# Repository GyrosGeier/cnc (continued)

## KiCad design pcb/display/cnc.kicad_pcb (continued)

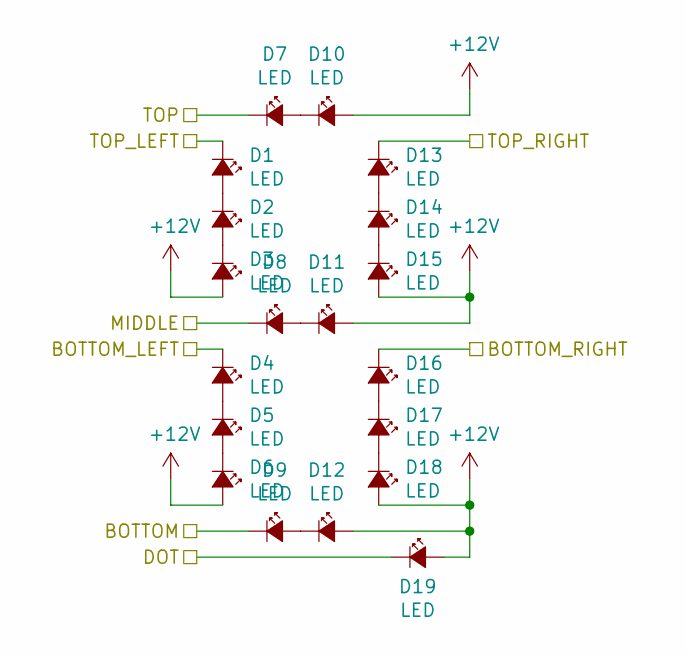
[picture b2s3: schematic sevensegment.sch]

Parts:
D1, D2, D3, D4, D5, D6, D7, D8, D9, D10, D11, D12, D13, D14, D15, D16, D17, D18, D19: LED; LED_Osram_LG_T770

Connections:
+12V: D3.2 (A), D6.2 (A), D10.2 (A), D11.2 (A), D12.2 (A), D15.2 (A), D18.2 (A), D19.2 (A); also elsewhere on the board
/display/display_x1_x2/sevensegment_1/BOTTOM: D9.1 (K); also elsewhere on the board
/display/display_x1_x2/sevensegment_1/BOTTOM_LEFT: D4.1 (K); also elsewhere on the board
/display/display_x1_x2/sevensegment_1/BOTTOM_RIGHT: D16.1 (K); also elsewhere on the board
/display/display_x1_x2/sevensegment_1/DOT: D19.1 (K); also elsewhere on the board
/display/display_x1_x2/sevensegment_1/MIDDLE: D8.1 (K); also elsewhere on the board
/display/display_x1_x2/sevensegment_1/TOP: D7.1 (K); also elsewhere on the board
/display/display_x1_x2/sevensegment_1/TOP_LEFT: D1.1 (K); also elsewhere on the board
/display/display_x1_x2/sevensegment_1/TOP_RIGHT: D13.1 (K); also elsewhere on the board
unnamed: D1.2 (A), D2.1 (K)
unnamed: D2.2 (A), D3.1 (K)
unnamed: D4.2 (A), D5.1 (K)
unnamed: D5.2 (A), D6.1 (K)
unnamed: D7.2 (A), D10.1 (K)
unnamed: D8.2 (A), D11.1 (K)
unnamed: D9.2 (A), D12.1 (K)
unnamed: D13.2 (A), D14.1 (K)
unnamed: D14.2 (A), D15.1 (K)
unnamed: D16.2 (A), D17.1 (K)
unnamed: D17.2 (A), D18.1 (K)

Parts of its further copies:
D20, D21, D22, D23, D24, D25, D26, D27, D28, D29, D30, D31, D32, D33, D34, D35, D36, D37, D38, D39, D40, D41, D42, D43, D44, D45, D46, D47, D48, D49, D50, D51, D52, D53, D54, D55, D56, D57, D58, D59, D60, D61, D62, D63, D64, D65, D66, D67, D68, D69, D70, D71, D72, D73, D74, D75, D76, D77, D78, D79, D80, D81, D82, D83, D84, D85, D86, D87, D88, D89, D90, D91, D92, D93, D94, D95, D96, D97, D98, D99, D100, D101, D102, D103, D104, D105, D106, D107, D108, D109, D110, D111, D112, D113, D114, D115, D116, D117, D118, D119, D120, D121, D122, D123, D124, D125, D126, D127, D128, D129, D130, D131, D132, D133, D134, D135, D136, D137, D138, D139, D140, D141, D142, D143, D144, D145, D146, D147, D148, D149, D150, D151, D152, D153, D154, D155, D156, D157, D158, D159, D160, D161, D162, D163, D164, D165, D166, D167, D168, D169, D170, D171, D172, D173, D174, D175, D176, D177, D178, D179, D180, D181, D182, D183, D184, D185, D186, D187, D188, D189, D190, D191, D192, D193, D194, D195, D196, D197, D198, D199, D200, D201, D202, D203, D204, D205, D206, D207, D208, D209, D210, D211, D212, D213, D214, D215, D216, D217, D218, D219, D220, D221, D222, D223, D224, D225, D226, D227, D228, D229, D230, D231, D232, D233, D234, D235, D236, D237, D238, D239, D240, D241, D242, D243, D244, D245, D246, D247, D248, D249, D250, D251, D252, D253, D254, D255, D256, D257, D258, D259, D260, D261, D262, D263, D264, D265, D266, D267, D268, D269, D270, D271, D272, D273, D274, D275, D276, D277, D278, D279, D280, D281, D282, D283, D284, D285, D286, D287, D288, D289, D290, D291, D292, D293, D294, D295, D296, D297, D298, D299, D300, D301, D302, D303, D304, D305, D306, D307, D308, D309, D310, D311, D312, D313, D314, D315, D316, D317, D318, D319, D320, D321, D322, D323, D324, D325, D326, D327, D328, D329, D330, D331, D332, D333, D334, D335, D336, D337, D338, D339, D340, D341, D342, D343, D344, D345, D346, D347, D348, D349, D350, D351, D352, D353, D354, D355, D356, D357, D358, D359, D360, D361, D362, D363, D364, D365, D366, D367, D368, D369, D370, D371, D372, D373, D374, D375, D376, D377, D378, D379, D380, D381, D382, D383, D384, D385, D386, D387, D388, D389, D390, D391, D392, D393, D394, D395, D396, D397, D398, D399, D400, D401, D402, D403, D404, D405, D406, D407, D408, D409, D410, D411, D412, D413, D414, D415, D416, D417, D418, D419, D420, D421, D422, D423, D424, D425, D426, D427, D428, D429, D430, D431, D432, D433, D434, D435, D436, D437, D438, D439, D440, D441, D442, D443, D444, D445, D446, D447, D448, D449, D450, D451, D452, D453, D454, D455, D456: LED; LED_Osram_LG_T770

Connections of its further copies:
+12V: D22.2 (A), D25.2 (A), D29.2 (A), D30.2 (A), D31.2 (A), D34.2 (A), D37.2 (A), D38.2 (A), D41.2 (A), D44.2 (A), D48.2 (A), D49.2 (A), D50.2 (A), D53.2 (A), D56.2 (A), D57.2 (A), D60.2 (A), D63.2 (A), D67.2 (A), D68.2 (A), D69.2 (A), D72.2 (A), D75.2 (A), D76.2 (A), D79.2 (A), D82.2 (A), D86.2 (A), D87.2 (A), D88.2 (A), D91.2 (A), D94.2 (A), D95.2 (A), D98.2 (A), D101.2 (A), D105.2 (A), D106.2 (A), D107.2 (A), D110.2 (A), D113.2 (A), D114.2 (A), D117.2 (A), D120.2 (A), D124.2 (A), D125.2 (A), D126.2 (A), D129.2 (A), D132.2 (A), D133.2 (A), D136.2 (A), D139.2 (A), D143.2 (A), D144.2 (A), D145.2 (A), D148.2 (A), D151.2 (A), D152.2 (A), D155.2 (A), D158.2 (A), D162.2 (A), D163.2 (A), D164.2 (A), D167.2 (A), D170.2 (A), D171.2 (A), D174.2 (A), D177.2 (A), D181.2 (A), D182.2 (A), D183.2 (A), D186.2 (A), D189.2 (A), D190.2 (A), D193.2 (A), D196.2 (A), D200.2 (A), D201.2 (A), D202.2 (A), D205.2 (A), D208.2 (A), D209.2 (A), D212.2 (A), D215.2 (A), D219.2 (A), D220.2 (A), D221.2 (A), D224.2 (A), D227.2 (A), D228.2 (A), D231.2 (A), D234.2 (A), D238.2 (A), D239.2 (A), D240.2 (A), D243.2 (A), D246.2 (A), D247.2 (A), D250.2 (A), D253.2 (A), D257.2 (A), D258.2 (A), D259.2 (A), D262.2 (A), D265.2 (A), D266.2 (A), D269.2 (A), D272.2 (A), D276.2 (A), D277.2 (A), D278.2 (A), D281.2 (A), D284.2 (A), D285.2 (A), D288.2 (A), D291.2 (A), D295.2 (A), D296.2 (A), D297.2 (A), D300.2 (A), D303.2 (A), D304.2 (A), D307.2 (A), D310.2 (A), D314.2 (A), D315.2 (A), D316.2 (A), D319.2 (A), D322.2 (A), D323.2 (A), D326.2 (A), D329.2 (A), D333.2 (A), D334.2 (A), D335.2 (A), D338.2 (A), D341.2 (A), D342.2 (A), D345.2 (A), D348.2 (A), D352.2 (A), D353.2 (A), D354.2 (A), D357.2 (A), D360.2 (A), D361.2 (A), D364.2 (A), D367.2 (A), D371.2 (A), D372.2 (A), D373.2 (A), D376.2 (A), D379.2 (A), D380.2 (A), D383.2 (A), D386.2 (A), D390.2 (A), D391.2 (A), D392.2 (A), D395.2 (A), D398.2 (A), D399.2 (A), D402.2 (A), D405.2 (A), D409.2 (A), D410.2 (A), D411.2 (A), D414.2 (A), D417.2 (A), D418.2 (A), D421.2 (A), D424.2 (A), D428.2 (A), D429.2 (A), D430.2 (A), D433.2 (A), D436.2 (A), D437.2 (A), D440.2 (A), D443.2 (A), D447.2 (A), D448.2 (A), D449.2 (A), D452.2 (A), D455.2 (A), D456.2 (A); also elsewhere on the board
/display/display_s1_s2/sevensegment_1/BOTTOM: D351.1 (K); also elsewhere on the board
/display/display_s1_s2/sevensegment_1/BOTTOM_LEFT: D346.1 (K); also elsewhere on the board
/display/display_s1_s2/sevensegment_1/BOTTOM_RIGHT: D358.1 (K); also elsewhere on the board
/display/display_s1_s2/sevensegment_1/DOT: D361.1 (K); also elsewhere on the board
/display/display_s1_s2/sevensegment_1/MIDDLE: D350.1 (K); also elsewhere on the board
/display/display_s1_s2/sevensegment_1/TOP: D349.1 (K); also elsewhere on the board
/display/display_s1_s2/sevensegment_1/TOP_LEFT: D343.1 (K); also elsewhere on the board
/display/display_s1_s2/sevensegment_1/TOP_RIGHT: D355.1 (K); also elsewhere on the board
/display/display_s1_s2/sevensegment_2/BOTTOM: D370.1 (K); also elsewhere on the board
/display/display_s1_s2/sevensegment_2/BOTTOM_LEFT: D365.1 (K); also elsewhere on the board
/display/display_s1_s2/sevensegment_2/BOTTOM_RIGHT: D377.1 (K); also elsewhere on the board
/display/display_s1_s2/sevensegment_2/DOT: D380.1 (K); also elsewhere on the board
/display/display_s1_s2/sevensegment_2/MIDDLE: D369.1 (K); also elsewhere on the board
/display/display_s1_s2/sevensegment_2/TOP: D368.1 (K); also elsewhere on the board
/display/display_s1_s2/sevensegment_2/TOP_LEFT: D362.1 (K); also elsewhere on the board
/display/display_s1_s2/sevensegment_2/TOP_RIGHT: D374.1 (K); also elsewhere on the board
/display/display_s3_s4/sevensegment_1/BOTTOM: D313.1 (K); also elsewhere on the board
/display/display_s3_s4/sevensegment_1/BOTTOM_LEFT: D308.1 (K); also elsewhere on the board
/display/display_s3_s4/sevensegment_1/BOTTOM_RIGHT: D320.1 (K); also elsewhere on the board
/display/display_s3_s4/sevensegment_1/DOT: D323.1 (K); also elsewhere on the board
/display/display_s3_s4/sevensegment_1/MIDDLE: D312.1 (K); also elsewhere on the board
/display/display_s3_s4/sevensegment_1/TOP: D311.1 (K); also elsewhere on the board
/display/display_s3_s4/sevensegment_1/TOP_LEFT: D305.1 (K); also elsewhere on the board
/display/display_s3_s4/sevensegment_1/TOP_RIGHT: D317.1 (K); also elsewhere on the board
/display/display_s3_s4/sevensegment_2/BOTTOM: D332.1 (K); also elsewhere on the board
/display/display_s3_s4/sevensegment_2/BOTTOM_LEFT: D327.1 (K); also elsewhere on the board
/display/display_s3_s4/sevensegment_2/BOTTOM_RIGHT: D339.1 (K); also elsewhere on the board
/display/display_s3_s4/sevensegment_2/DOT: D342.1 (K); also elsewhere on the board
/display/display_s3_s4/sevensegment_2/MIDDLE: D331.1 (K); also elsewhere on the board
/display/display_s3_s4/sevensegment_2/TOP: D330.1 (K); also elsewhere on the board
/display/display_s3_s4/sevensegment_2/TOP_LEFT: D324.1 (K); also elsewhere on the board
/display/display_s3_s4/sevensegment_2/TOP_RIGHT: D336.1 (K); also elsewhere on the board
/display/display_s/sevensegment_1/BOTTOM: D427.1 (K); also elsewhere on the board
/display/display_s/sevensegment_1/BOTTOM_LEFT: D422.1 (K); also elsewhere on the board
/display/display_s/sevensegment_1/BOTTOM_RIGHT: D434.1 (K); also elsewhere on the board
/display/display_s/sevensegment_1/DOT: D437.1 (K); also elsewhere on the board
/display/display_s/sevensegment_1/MIDDLE: D426.1 (K); also elsewhere on the board
/display/display_s/sevensegment_1/TOP: D425.1 (K); also elsewhere on the board
/display/display_s/sevensegment_1/TOP_LEFT: D419.1 (K); also elsewhere on the board
/display/display_s/sevensegment_1/TOP_RIGHT: D431.1 (K); also elsewhere on the board
/display/display_s/sevensegment_2/BOTTOM: D446.1 (K); also elsewhere on the board
/display/display_s/sevensegment_2/BOTTOM_LEFT: D441.1 (K); also elsewhere on the board
/display/display_s/sevensegment_2/BOTTOM_RIGHT: D453.1 (K); also elsewhere on the board
/display/display_s/sevensegment_2/DOT: D456.1 (K); also elsewhere on the board
/display/display_s/sevensegment_2/MIDDLE: D445.1 (K); also elsewhere on the board
/display/display_s/sevensegment_2/TOP: D444.1 (K); also elsewhere on the board
/display/display_s/sevensegment_2/TOP_LEFT: D438.1 (K); also elsewhere on the board
/display/display_s/sevensegment_2/TOP_RIGHT: D450.1 (K); also elsewhere on the board
/display/display_x1_x2/sevensegment_2/BOTTOM: D28.1 (K); also elsewhere on the board
/display/display_x1_x2/sevensegment_2/BOTTOM_LEFT: D23.1 (K); also elsewhere on the board
/display/display_x1_x2/sevensegment_2/BOTTOM_RIGHT: D35.1 (K); also elsewhere on the board
/display/display_x1_x2/sevensegment_2/DOT: D38.1 (K); also elsewhere on the board
/display/display_x1_x2/sevensegment_2/MIDDLE: D27.1 (K); also elsewhere on the board
/display/display_x1_x2/sevensegment_2/TOP: D26.1 (K); also elsewhere on the board
/display/display_x1_x2/sevensegment_2/TOP_LEFT: D20.1 (K); also elsewhere on the board
/display/display_x1_x2/sevensegment_2/TOP_RIGHT: D32.1 (K); also elsewhere on the board
/display/display_x3_x4/sevensegment_1/BOTTOM: D47.1 (K); also elsewhere on the board
/display/display_x3_x4/sevensegment_1/BOTTOM_LEFT: D42.1 (K); also elsewhere on the board
/display/display_x3_x4/sevensegment_1/BOTTOM_RIGHT: D54.1 (K); also elsewhere on the board
/display/display_x3_x4/sevensegment_1/DOT: D57.1 (K); also elsewhere on the board
/display/display_x3_x4/sevensegment_1/MIDDLE: D46.1 (K); also elsewhere on the board
/display/display_x3_x4/sevensegment_1/TOP: D45.1 (K); also elsewhere on the board
/display/display_x3_x4/sevensegment_1/TOP_LEFT: D39.1 (K); also elsewhere on the board
/display/display_x3_x4/sevensegment_1/TOP_RIGHT: D51.1 (K); also elsewhere on the board
/display/display_x3_x4/sevensegment_2/BOTTOM: D66.1 (K); also elsewhere on the board
/display/display_x3_x4/sevensegment_2/BOTTOM_LEFT: D61.1 (K); also elsewhere on the board
/display/display_x3_x4/sevensegment_2/BOTTOM_RIGHT: D73.1 (K); also elsewhere on the board
/display/display_x3_x4/sevensegment_2/DOT: D76.1 (K); also elsewhere on the board
/display/display_x3_x4/sevensegment_2/MIDDLE: D65.1 (K); also elsewhere on the board
/display/display_x3_x4/sevensegment_2/TOP: D64.1 (K); also elsewhere on the board
/display/display_x3_x4/sevensegment_2/TOP_LEFT: D58.1 (K); also elsewhere on the board
/display/display_x3_x4/sevensegment_2/TOP_RIGHT: D70.1 (K); also elsewhere on the board
/display/display_x5_y5/sevensegment_1/BOTTOM: D85.1 (K); also elsewhere on the board
/display/display_x5_y5/sevensegment_1/BOTTOM_LEFT: D80.1 (K); also elsewhere on the board
/display/display_x5_y5/sevensegment_1/BOTTOM_RIGHT: D92.1 (K); also elsewhere on the board
/display/display_x5_y5/sevensegment_1/DOT: D95.1 (K); also elsewhere on the board
/display/display_x5_y5/sevensegment_1/MIDDLE: D84.1 (K); also elsewhere on the board
/display/display_x5_y5/sevensegment_1/TOP: D83.1 (K); also elsewhere on the board
/display/display_x5_y5/sevensegment_1/TOP_LEFT: D77.1 (K); also elsewhere on the board
/display/display_x5_y5/sevensegment_1/TOP_RIGHT: D89.1 (K); also elsewhere on the board
/display/display_x5_y5/sevensegment_2/BOTTOM: D104.1 (K); also elsewhere on the board
/display/display_x5_y5/sevensegment_2/BOTTOM_LEFT: D99.1 (K); also elsewhere on the board
/display/display_x5_y5/sevensegment_2/BOTTOM_RIGHT: D111.1 (K); also elsewhere on the board
/display/display_x5_y5/sevensegment_2/DOT: D114.1 (K); also elsewhere on the board
/display/display_x5_y5/sevensegment_2/MIDDLE: D103.1 (K); also elsewhere on the board
/display/display_x5_y5/sevensegment_2/TOP: D102.1 (K); also elsewhere on the board
/display/display_x5_y5/sevensegment_2/TOP_LEFT: D96.1 (K); also elsewhere on the board
/display/display_x5_y5/sevensegment_2/TOP_RIGHT: D108.1 (K); also elsewhere on the board
/display/display_y1_y2/sevensegment_1/BOTTOM: D161.1 (K); also elsewhere on the board
/display/display_y1_y2/sevensegment_1/BOTTOM_LEFT: D156.1 (K); also elsewhere on the board
/display/display_y1_y2/sevensegment_1/BOTTOM_RIGHT: D168.1 (K); also elsewhere on the board
/display/display_y1_y2/sevensegment_1/DOT: D171.1 (K); also elsewhere on the board
/display/display_y1_y2/sevensegment_1/MIDDLE: D160.1 (K); also elsewhere on the board
/display/display_y1_y2/sevensegment_1/TOP: D159.1 (K); also elsewhere on the board
/display/display_y1_y2/sevensegment_1/TOP_LEFT: D153.1 (K); also elsewhere on the board
/display/display_y1_y2/sevensegment_1/TOP_RIGHT: D165.1 (K); also elsewhere on the board
/display/display_y1_y2/sevensegment_2/BOTTOM: D180.1 (K); also elsewhere on the board
/display/display_y1_y2/sevensegment_2/BOTTOM_LEFT: D175.1 (K); also elsewhere on the board
/display/display_y1_y2/sevensegment_2/BOTTOM_RIGHT: D187.1 (K); also elsewhere on the board
/display/display_y1_y2/sevensegment_2/DOT: D190.1 (K); also elsewhere on the board
/display/display_y1_y2/sevensegment_2/MIDDLE: D179.1 (K); also elsewhere on the board
/display/display_y1_y2/sevensegment_2/TOP: D178.1 (K); also elsewhere on the board
/display/display_y1_y2/sevensegment_2/TOP_LEFT: D172.1 (K); also elsewhere on the board
/display/display_y1_y2/sevensegment_2/TOP_RIGHT: D184.1 (K); also elsewhere on the board
/display/display_y3_y4/sevensegment_1/BOTTOM: D123.1 (K); also elsewhere on the board
/display/display_y3_y4/sevensegment_1/BOTTOM_LEFT: D118.1 (K); also elsewhere on the board
/display/display_y3_y4/sevensegment_1/BOTTOM_RIGHT: D130.1 (K); also elsewhere on the board
/display/display_y3_y4/sevensegment_1/DOT: D133.1 (K); also elsewhere on the board
/display/display_y3_y4/sevensegment_1/MIDDLE: D122.1 (K); also elsewhere on the board
/display/display_y3_y4/sevensegment_1/TOP: D121.1 (K); also elsewhere on the board
/display/display_y3_y4/sevensegment_1/TOP_LEFT: D115.1 (K); also elsewhere on the board
/display/display_y3_y4/sevensegment_1/TOP_RIGHT: D127.1 (K); also elsewhere on the board
/display/display_y3_y4/sevensegment_2/BOTTOM: D142.1 (K); also elsewhere on the board
/display/display_y3_y4/sevensegment_2/BOTTOM_LEFT: D137.1 (K); also elsewhere on the board
/display/display_y3_y4/sevensegment_2/BOTTOM_RIGHT: D149.1 (K); also elsewhere on the board
/display/display_y3_y4/sevensegment_2/DOT: D152.1 (K); also elsewhere on the board
/display/display_y3_y4/sevensegment_2/MIDDLE: D141.1 (K); also elsewhere on the board
/display/display_y3_y4/sevensegment_2/TOP: D140.1 (K); also elsewhere on the board
/display/display_y3_y4/sevensegment_2/TOP_LEFT: D134.1 (K); also elsewhere on the board
/display/display_y3_y4/sevensegment_2/TOP_RIGHT: D146.1 (K); also elsewhere on the board
/display/display_y/sevensegment_1/BOTTOM: D389.1 (K); also elsewhere on the board
/display/display_y/sevensegment_1/BOTTOM_LEFT: D384.1 (K); also elsewhere on the board
/display/display_y/sevensegment_1/BOTTOM_RIGHT: D396.1 (K); also elsewhere on the board
/display/display_y/sevensegment_1/DOT: D399.1 (K); also elsewhere on the board
/display/display_y/sevensegment_1/MIDDLE: D388.1 (K); also elsewhere on the board
/display/display_y/sevensegment_1/TOP: D387.1 (K); also elsewhere on the board
/display/display_y/sevensegment_1/TOP_LEFT: D381.1 (K); also elsewhere on the board
/display/display_y/sevensegment_1/TOP_RIGHT: D393.1 (K); also elsewhere on the board
/display/display_y/sevensegment_2/BOTTOM: D408.1 (K); also elsewhere on the board
/display/display_y/sevensegment_2/BOTTOM_LEFT: D403.1 (K); also elsewhere on the board
/display/display_y/sevensegment_2/BOTTOM_RIGHT: D415.1 (K); also elsewhere on the board
/display/display_y/sevensegment_2/DOT: D418.1 (K); also elsewhere on the board
/display/display_y/sevensegment_2/MIDDLE: D407.1 (K); also elsewhere on the board
/display/display_y/sevensegment_2/TOP: D406.1 (K); also elsewhere on the board
/display/display_y/sevensegment_2/TOP_LEFT: D400.1 (K); also elsewhere on the board
/display/display_y/sevensegment_2/TOP_RIGHT: D412.1 (K); also elsewhere on the board
/display/display_z1_z2/sevensegment_1/BOTTOM: D199.1 (K); also elsewhere on the board
/display/display_z1_z2/sevensegment_1/BOTTOM_LEFT: D194.1 (K); also elsewhere on the board
/display/display_z1_z2/sevensegment_1/BOTTOM_RIGHT: D206.1 (K); also elsewhere on the board
/display/display_z1_z2/sevensegment_1/DOT: D209.1 (K); also elsewhere on the board
/display/display_z1_z2/sevensegment_1/MIDDLE: D198.1 (K); also elsewhere on the board
/display/display_z1_z2/sevensegment_1/TOP: D197.1 (K); also elsewhere on the board
/display/display_z1_z2/sevensegment_1/TOP_LEFT: D191.1 (K); also elsewhere on the board
/display/display_z1_z2/sevensegment_1/TOP_RIGHT: D203.1 (K); also elsewhere on the board
/display/display_z1_z2/sevensegment_2/BOTTOM: D218.1 (K); also elsewhere on the board
/display/display_z1_z2/sevensegment_2/BOTTOM_LEFT: D213.1 (K); also elsewhere on the board
/display/display_z1_z2/sevensegment_2/BOTTOM_RIGHT: D225.1 (K); also elsewhere on the board
/display/display_z1_z2/sevensegment_2/DOT: D228.1 (K); also elsewhere on the board
/display/display_z1_z2/sevensegment_2/MIDDLE: D217.1 (K); also elsewhere on the board
/display/display_z1_z2/sevensegment_2/TOP: D216.1 (K); also elsewhere on the board
/display/display_z1_z2/sevensegment_2/TOP_LEFT: D210.1 (K); also elsewhere on the board
/display/display_z1_z2/sevensegment_2/TOP_RIGHT: D222.1 (K); also elsewhere on the board
/display/display_z3_z4/sevensegment_1/BOTTOM: D237.1 (K); also elsewhere on the board
/display/display_z3_z4/sevensegment_1/BOTTOM_LEFT: D232.1 (K); also elsewhere on the board
/display/display_z3_z4/sevensegment_1/BOTTOM_RIGHT: D244.1 (K); also elsewhere on the board
/display/display_z3_z4/sevensegment_1/DOT: D247.1 (K); also elsewhere on the board
/display/display_z3_z4/sevensegment_1/MIDDLE: D236.1 (K); also elsewhere on the board
/display/display_z3_z4/sevensegment_1/TOP: D235.1 (K); also elsewhere on the board
/display/display_z3_z4/sevensegment_1/TOP_LEFT: D229.1 (K); also elsewhere on the board
/display/display_z3_z4/sevensegment_1/TOP_RIGHT: D241.1 (K); also elsewhere on the board
/display/display_z3_z4/sevensegment_2/BOTTOM: D256.1 (K); also elsewhere on the board
/display/display_z3_z4/sevensegment_2/BOTTOM_LEFT: D251.1 (K); also elsewhere on the board
/display/display_z3_z4/sevensegment_2/BOTTOM_RIGHT: D263.1 (K); also elsewhere on the board
/display/display_z3_z4/sevensegment_2/DOT: D266.1 (K); also elsewhere on the board
/display/display_z3_z4/sevensegment_2/MIDDLE: D255.1 (K); also elsewhere on the board
/display/display_z3_z4/sevensegment_2/TOP: D254.1 (K); also elsewhere on the board
/display/display_z3_z4/sevensegment_2/TOP_LEFT: D248.1 (K); also elsewhere on the board
/display/display_z3_z4/sevensegment_2/TOP_RIGHT: D260.1 (K); also elsewhere on the board
/display/display_z5_s5/sevensegment_1/BOTTOM: D275.1 (K); also elsewhere on the board
/display/display_z5_s5/sevensegment_1/BOTTOM_LEFT: D270.1 (K); also elsewhere on the board
/display/display_z5_s5/sevensegment_1/BOTTOM_RIGHT: D282.1 (K); also elsewhere on the board
/display/display_z5_s5/sevensegment_1/DOT: D285.1 (K); also elsewhere on the board
/display/display_z5_s5/sevensegment_1/MIDDLE: D274.1 (K); also elsewhere on the board
/display/display_z5_s5/sevensegment_1/TOP: D273.1 (K); also elsewhere on the board
/display/display_z5_s5/sevensegment_1/TOP_LEFT: D267.1 (K); also elsewhere on the board
/display/display_z5_s5/sevensegment_1/TOP_RIGHT: D279.1 (K); also elsewhere on the board
/display/display_z5_s5/sevensegment_2/BOTTOM: D294.1 (K); also elsewhere on the board
/display/display_z5_s5/sevensegment_2/BOTTOM_LEFT: D289.1 (K); also elsewhere on the board
/display/display_z5_s5/sevensegment_2/BOTTOM_RIGHT: D301.1 (K); also elsewhere on the board
/display/display_z5_s5/sevensegment_2/DOT: D304.1 (K); also elsewhere on the board
/display/display_z5_s5/sevensegment_2/MIDDLE: D293.1 (K); also elsewhere on the board
/display/display_z5_s5/sevensegment_2/TOP: D292.1 (K); also elsewhere on the board
/display/display_z5_s5/sevensegment_2/TOP_LEFT: D286.1 (K); also elsewhere on the board
/display/display_z5_s5/sevensegment_2/TOP_RIGHT: D298.1 (K); also elsewhere on the board
unnamed: D20.2 (A), D21.1 (K)
unnamed: D21.2 (A), D22.1 (K)
unnamed: D23.2 (A), D24.1 (K)
unnamed: D24.2 (A), D25.1 (K)
unnamed: D26.2 (A), D29.1 (K)
unnamed: D27.2 (A), D30.1 (K)
unnamed: D28.2 (A), D31.1 (K)
unnamed: D32.2 (A), D33.1 (K)
unnamed: D33.2 (A), D34.1 (K)
unnamed: D35.2 (A), D36.1 (K)
unnamed: D36.2 (A), D37.1 (K)
unnamed: D39.2 (A), D40.1 (K)
unnamed: D40.2 (A), D41.1 (K)
unnamed: D42.2 (A), D43.1 (K)
unnamed: D43.2 (A), D44.1 (K)
unnamed: D45.2 (A), D48.1 (K)
unnamed: D46.2 (A), D49.1 (K)
unnamed: D47.2 (A), D50.1 (K)
unnamed: D51.2 (A), D52.1 (K)
unnamed: D52.2 (A), D53.1 (K)
unnamed: D54.2 (A), D55.1 (K)
unnamed: D55.2 (A), D56.1 (K)
unnamed: D58.2 (A), D59.1 (K)
unnamed: D59.2 (A), D60.1 (K)
unnamed: D61.2 (A), D62.1 (K)
unnamed: D62.2 (A), D63.1 (K)
unnamed: D64.2 (A), D67.1 (K)
unnamed: D65.2 (A), D68.1 (K)
unnamed: D66.2 (A), D69.1 (K)
unnamed: D70.2 (A), D71.1 (K)
unnamed: D71.2 (A), D72.1 (K)
unnamed: D73.2 (A), D74.1 (K)
unnamed: D74.2 (A), D75.1 (K)
unnamed: D77.2 (A), D78.1 (K)
unnamed: D78.2 (A), D79.1 (K)
unnamed: D80.2 (A), D81.1 (K)
unnamed: D81.2 (A), D82.1 (K)
unnamed: D83.2 (A), D86.1 (K)
unnamed: D84.2 (A), D87.1 (K)
unnamed: D85.2 (A), D88.1 (K)
unnamed: D89.2 (A), D90.1 (K)
unnamed: D90.2 (A), D91.1 (K)
unnamed: D92.2 (A), D93.1 (K)
unnamed: D93.2 (A), D94.1 (K)
unnamed: D96.2 (A), D97.1 (K)
unnamed: D97.2 (A), D98.1 (K)
unnamed: D99.2 (A), D100.1 (K)
unnamed: D100.2 (A), D101.1 (K)
unnamed: D102.2 (A), D105.1 (K)
unnamed: D103.2 (A), D106.1 (K)
unnamed: D104.2 (A), D107.1 (K)
unnamed: D108.2 (A), D109.1 (K)
unnamed: D109.2 (A), D110.1 (K)
unnamed: D111.2 (A), D112.1 (K)
unnamed: D112.2 (A), D113.1 (K)
unnamed: D115.2 (A), D116.1 (K)
unnamed: D116.2 (A), D117.1 (K)
unnamed: D118.2 (A), D119.1 (K)
unnamed: D119.2 (A), D120.1 (K)
unnamed: D121.2 (A), D124.1 (K)
unnamed: D122.2 (A), D125.1 (K)
unnamed: D123.2 (A), D126.1 (K)
unnamed: D127.2 (A), D128.1 (K)
unnamed: D128.2 (A), D129.1 (K)
unnamed: D130.2 (A), D131.1 (K)
unnamed: D131.2 (A), D132.1 (K)
unnamed: D134.2 (A), D135.1 (K)
unnamed: D135.2 (A), D136.1 (K)
unnamed: D137.2 (A), D138.1 (K)
unnamed: D138.2 (A), D139.1 (K)
unnamed: D140.2 (A), D143.1 (K)
unnamed: D141.2 (A), D144.1 (K)
unnamed: D142.2 (A), D145.1 (K)
unnamed: D146.2 (A), D147.1 (K)
unnamed: D147.2 (A), D148.1 (K)
unnamed: D149.2 (A), D150.1 (K)
unnamed: D150.2 (A), D151.1 (K)
unnamed: D153.2 (A), D154.1 (K)
unnamed: D154.2 (A), D155.1 (K)
unnamed: D156.2 (A), D157.1 (K)
unnamed: D157.2 (A), D158.1 (K)
unnamed: D159.2 (A), D162.1 (K)
unnamed: D160.2 (A), D163.1 (K)
unnamed: D161.2 (A), D164.1 (K)
unnamed: D165.2 (A), D166.1 (K)
unnamed: D166.2 (A), D167.1 (K)
unnamed: D168.2 (A), D169.1 (K)
unnamed: D169.2 (A), D170.1 (K)
unnamed: D172.2 (A), D173.1 (K)
unnamed: D173.2 (A), D174.1 (K)
unnamed: D175.2 (A), D176.1 (K)
unnamed: D176.2 (A), D177.1 (K)
unnamed: D178.2 (A), D181.1 (K)
unnamed: D179.2 (A), D182.1 (K)
unnamed: D180.2 (A), D183.1 (K)
unnamed: D184.2 (A), D185.1 (K)
unnamed: D185.2 (A), D186.1 (K)
unnamed: D187.2 (A), D188.1 (K)
unnamed: D188.2 (A), D189.1 (K)
unnamed: D191.2 (A), D192.1 (K)
unnamed: D192.2 (A), D193.1 (K)
unnamed: D194.2 (A), D195.1 (K)
unnamed: D195.2 (A), D196.1 (K)
unnamed: D197.2 (A), D200.1 (K)
unnamed: D198.2 (A), D201.1 (K)
unnamed: D199.2 (A), D202.1 (K)
unnamed: D203.2 (A), D204.1 (K)
unnamed: D204.2 (A), D205.1 (K)
unnamed: D206.2 (A), D207.1 (K)
unnamed: D207.2 (A), D208.1 (K)
unnamed: D210.2 (A), D211.1 (K)
unnamed: D211.2 (A), D212.1 (K)
unnamed: D213.2 (A), D214.1 (K)
unnamed: D214.2 (A), D215.1 (K)
unnamed: D216.2 (A), D219.1 (K)
unnamed: D217.2 (A), D220.1 (K)
unnamed: D218.2 (A), D221.1 (K)
unnamed: D222.2 (A), D223.1 (K)
unnamed: D223.2 (A), D224.1 (K)
unnamed: D225.2 (A), D226.1 (K)
unnamed: D226.2 (A), D227.1 (K)
unnamed: D229.2 (A), D230.1 (K)
unnamed: D230.2 (A), D231.1 (K)
unnamed: D232.2 (A), D233.1 (K)
unnamed: D233.2 (A), D234.1 (K)
unnamed: D235.2 (A), D238.1 (K)
unnamed: D236.2 (A), D239.1 (K)
unnamed: D237.2 (A), D240.1 (K)
unnamed: D241.2 (A), D242.1 (K)
unnamed: D242.2 (A), D243.1 (K)
unnamed: D244.2 (A), D245.1 (K)
unnamed: D245.2 (A), D246.1 (K)
unnamed: D248.2 (A), D249.1 (K)
unnamed: D249.2 (A), D250.1 (K)
unnamed: D251.2 (A), D252.1 (K)
unnamed: D252.2 (A), D253.1 (K)
unnamed: D254.2 (A), D257.1 (K)
unnamed: D255.2 (A), D258.1 (K)
unnamed: D256.2 (A), D259.1 (K)
unnamed: D260.2 (A), D261.1 (K)
unnamed: D261.2 (A), D262.1 (K)
unnamed: D263.2 (A), D264.1 (K)
unnamed: D264.2 (A), D265.1 (K)
unnamed: D267.2 (A), D268.1 (K)
unnamed: D268.2 (A), D269.1 (K)
unnamed: D270.2 (A), D271.1 (K)
unnamed: D271.2 (A), D272.1 (K)
unnamed: D273.2 (A), D276.1 (K)
unnamed: D274.2 (A), D277.1 (K)
unnamed: D275.2 (A), D278.1 (K)
unnamed: D279.2 (A), D280.1 (K)
unnamed: D280.2 (A), D281.1 (K)
unnamed: D282.2 (A), D283.1 (K)
unnamed: D283.2 (A), D284.1 (K)
unnamed: D286.2 (A), D287.1 (K)
unnamed: D287.2 (A), D288.1 (K)
unnamed: D289.2 (A), D290.1 (K)
unnamed: D290.2 (A), D291.1 (K)
unnamed: D292.2 (A), D295.1 (K)
unnamed: D293.2 (A), D296.1 (K)
unnamed: D294.2 (A), D297.1 (K)
unnamed: D298.2 (A), D299.1 (K)
unnamed: D299.2 (A), D300.1 (K)
unnamed: D301.2 (A), D302.1 (K)
unnamed: D302.2 (A), D303.1 (K)
unnamed: D305.2 (A), D306.1 (K)
unnamed: D306.2 (A), D307.1 (K)
unnamed: D308.2 (A), D309.1 (K)
unnamed: D309.2 (A), D310.1 (K)
unnamed: D311.2 (A), D314.1 (K)
unnamed: D312.2 (A), D315.1 (K)
unnamed: D313.2 (A), D316.1 (K)
unnamed: D317.2 (A), D318.1 (K)
unnamed: D318.2 (A), D319.1 (K)
unnamed: D320.2 (A), D321.1 (K)
unnamed: D321.2 (A), D322.1 (K)
unnamed: D324.2 (A), D325.1 (K)
unnamed: D325.2 (A), D326.1 (K)
unnamed: D327.2 (A), D328.1 (K)
unnamed: D328.2 (A), D329.1 (K)
unnamed: D330.2 (A), D333.1 (K)
unnamed: D331.2 (A), D334.1 (K)
unnamed: D332.2 (A), D335.1 (K)
unnamed: D336.2 (A), D337.1 (K)
unnamed: D337.2 (A), D338.1 (K)
unnamed: D339.2 (A), D340.1 (K)
unnamed: D340.2 (A), D341.1 (K)
unnamed: D343.2 (A), D344.1 (K)
unnamed: D344.2 (A), D345.1 (K)
unnamed: D346.2 (A), D347.1 (K)
unnamed: D347.2 (A), D348.1 (K)
unnamed: D349.2 (A), D352.1 (K)
unnamed: D350.2 (A), D353.1 (K)
unnamed: D351.2 (A), D354.1 (K)
unnamed: D355.2 (A), D356.1 (K)
unnamed: D356.2 (A), D357.1 (K)
unnamed: D358.2 (A), D359.1 (K)
unnamed: D359.2 (A), D360.1 (K)
unnamed: D362.2 (A), D363.1 (K)
unnamed: D363.2 (A), D364.1 (K)
unnamed: D365.2 (A), D366.1 (K)
unnamed: D366.2 (A), D367.1 (K)
unnamed: D368.2 (A), D371.1 (K)
unnamed: D369.2 (A), D372.1 (K)
unnamed: D370.2 (A), D373.1 (K)
unnamed: D374.2 (A), D375.1 (K)
unnamed: D375.2 (A), D376.1 (K)
unnamed: D377.2 (A), D378.1 (K)
unnamed: D378.2 (A), D379.1 (K)
unnamed: D381.2 (A), D382.1 (K)
unnamed: D382.2 (A), D383.1 (K)
unnamed: D384.2 (A), D385.1 (K)
unnamed: D385.2 (A), D386.1 (K)
unnamed: D387.2 (A), D390.1 (K)
unnamed: D388.2 (A), D391.1 (K)
unnamed: D389.2 (A), D392.1 (K)
unnamed: D393.2 (A), D394.1 (K)
unnamed: D394.2 (A), D395.1 (K)
unnamed: D396.2 (A), D397.1 (K)
unnamed: D397.2 (A), D398.1 (K)
unnamed: D400.2 (A), D401.1 (K)
unnamed: D401.2 (A), D402.1 (K)
unnamed: D403.2 (A), D404.1 (K)
unnamed: D404.2 (A), D405.1 (K)
unnamed: D406.2 (A), D409.1 (K)
unnamed: D407.2 (A), D410.1 (K)
unnamed: D408.2 (A), D411.1 (K)
unnamed: D412.2 (A), D413.1 (K)
unnamed: D413.2 (A), D414.1 (K)
unnamed: D415.2 (A), D416.1 (K)
unnamed: D416.2 (A), D417.1 (K)
unnamed: D419.2 (A), D420.1 (K)
unnamed: D420.2 (A), D421.1 (K)
unnamed: D422.2 (A), D423.1 (K)
unnamed: D423.2 (A), D424.1 (K)
unnamed: D425.2 (A), D428.1 (K)
unnamed: D426.2 (A), D429.1 (K)
unnamed: D427.2 (A), D430.1 (K)
unnamed: D431.2 (A), D432.1 (K)
unnamed: D432.2 (A), D433.1 (K)
unnamed: D434.2 (A), D435.1 (K)
unnamed: D435.2 (A), D436.1 (K)
unnamed: D438.2 (A), D439.1 (K)
unnamed: D439.2 (A), D440.1 (K)
unnamed: D441.2 (A), D442.1 (K)
unnamed: D442.2 (A), D443.1 (K)
unnamed: D444.2 (A), D447.1 (K)
unnamed: D445.2 (A), D448.1 (K)
unnamed: D446.2 (A), D449.1 (K)
unnamed: D450.2 (A), D451.1 (K)
unnamed: D451.2 (A), D452.1 (K)
unnamed: D453.2 (A), D454.1 (K)
unnamed: D454.2 (A), D455.1 (K)

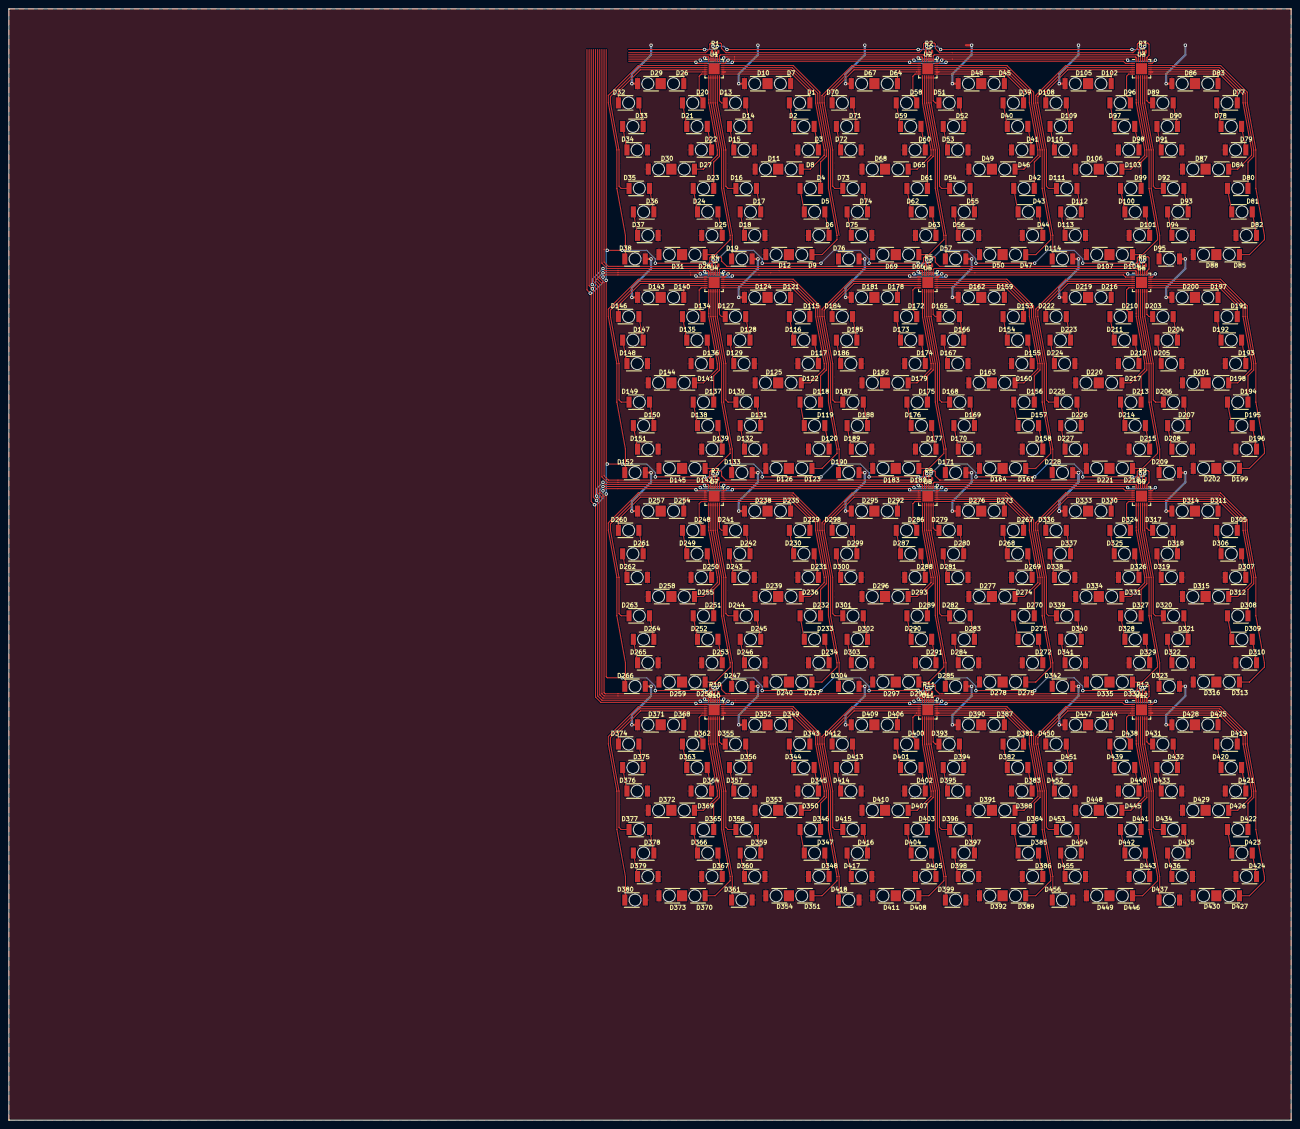
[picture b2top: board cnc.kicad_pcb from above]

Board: 2 copper layers, 300.0 x 260.0 mm, 480 parts (0 on the bottom side), 482 nets.

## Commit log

2016-09-16 Work in Progress
2016-09-20 Add Altera and ISSI libraries
